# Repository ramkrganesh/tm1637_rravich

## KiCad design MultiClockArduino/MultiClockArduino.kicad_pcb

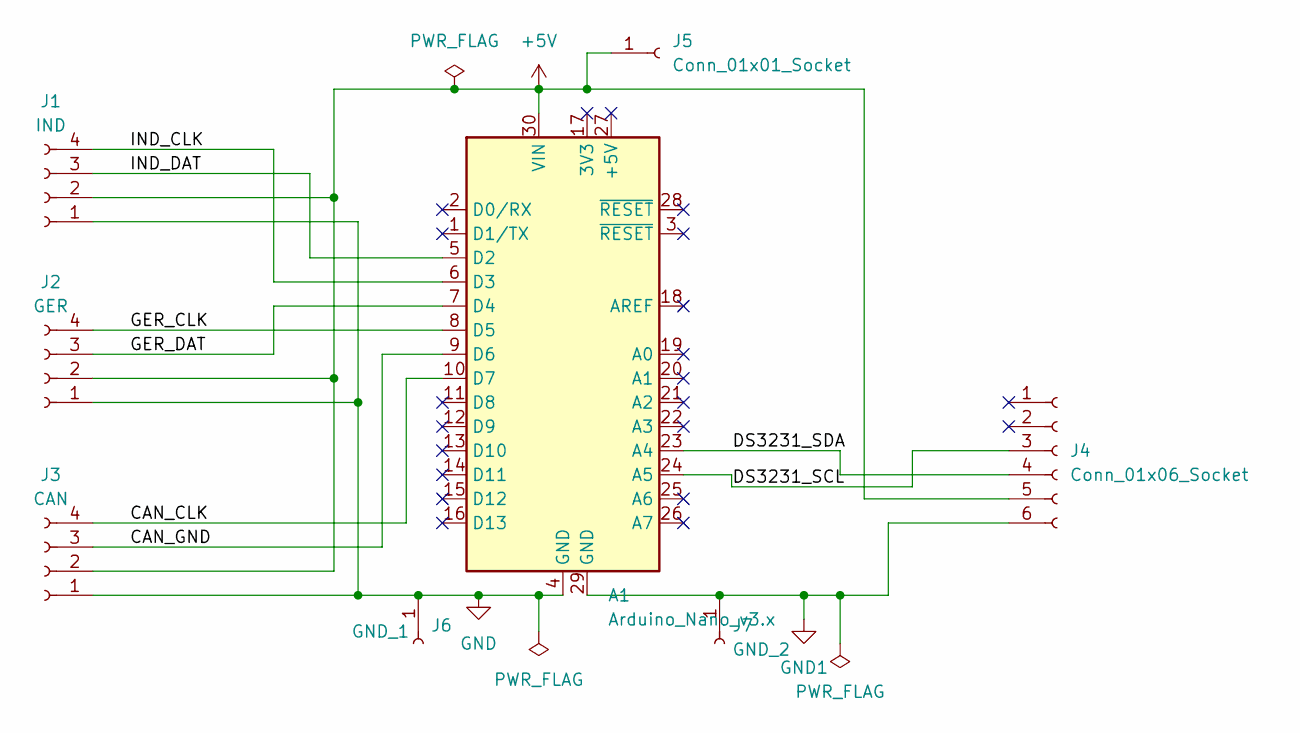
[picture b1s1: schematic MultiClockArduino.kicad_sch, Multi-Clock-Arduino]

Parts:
A1: Arduino_Nano_v3.x; Arduino_Nano
J1: IND; PinSocket_1x04_P2.54mm_Vertical
J2: GER; PinSocket_1x04_P2.54mm_Vertical
J3: CAN; PinSocket_1x04_P2.54mm_Vertical
J4: Conn_01x06_Socket; PinSocket_1x06_P2.54mm_Vertical
J5: Conn_01x01_Socket; PinSocket_1x01_P2.54mm_Vertical
J6: GND_1; PinSocket_1x01_P2.54mm_Vertical
J7: GND_2; PinSocket_1x01_P2.54mm_Vertical

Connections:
+5V: A1.30 (VIN), J1.2, J2.2, J3.2, J4.5, J5.1
/CAN_CLK: A1.10 (D7), J3.4
/CAN_GND: A1.9 (D6), J3.3
/DS3231_SCL: A1.24 (A5), J4.3
/DS3231_SDA: A1.23 (A4), J4.4
/GER_CLK: A1.8 (D5), J2.4
/GER_DAT: A1.7 (D4), J2.3
/IND_CLK: A1.6 (D3), J1.4
/IND_DAT: A1.5 (D2), J1.3
GND: A1.4 (GND), J1.1, J2.1, J3.1, J6.1
GND1: A1.29 (GND), J4.6, J7.1

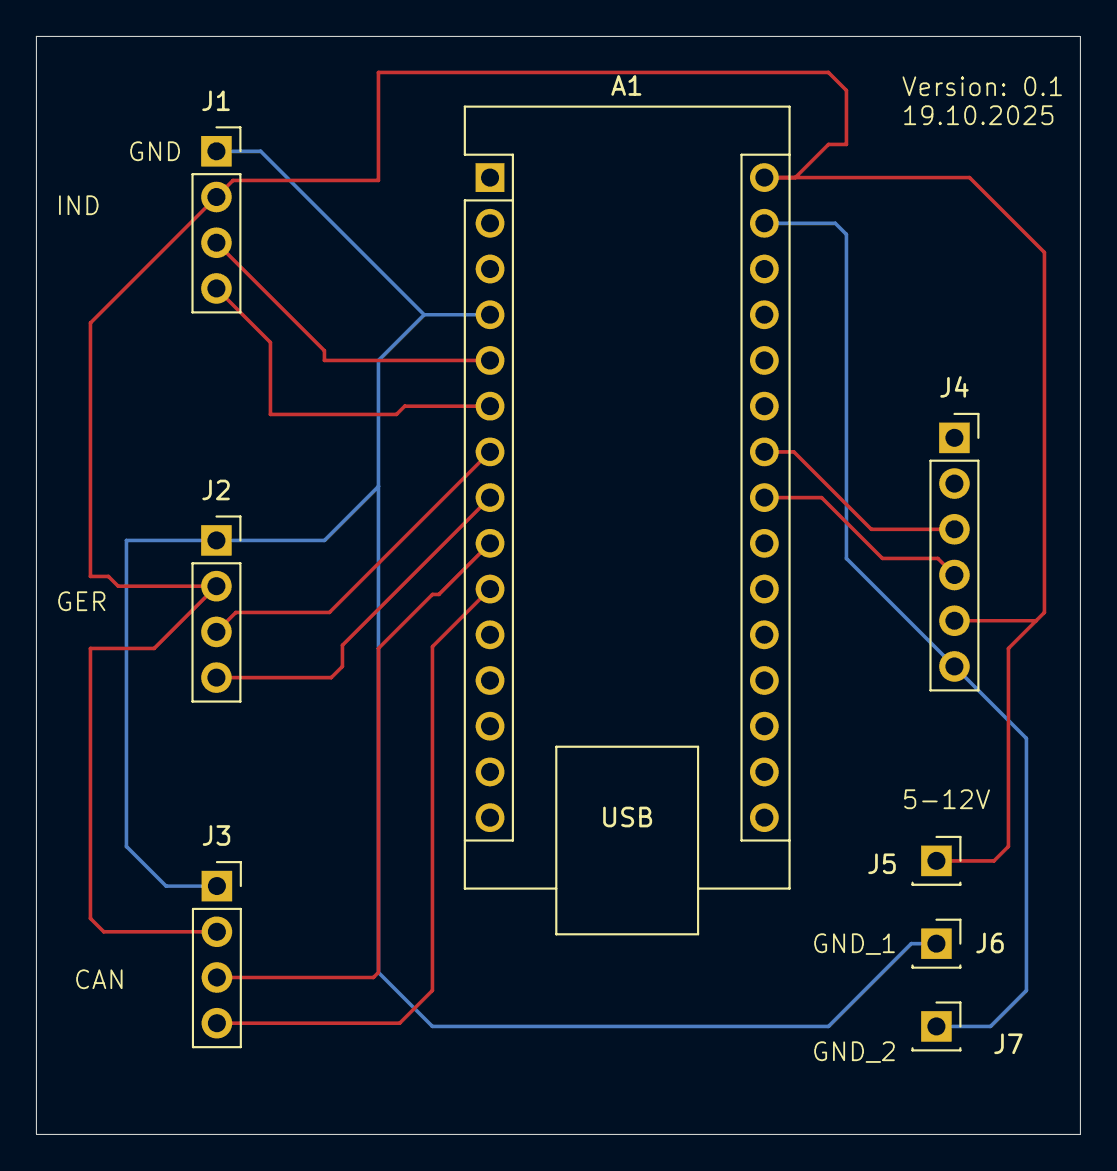
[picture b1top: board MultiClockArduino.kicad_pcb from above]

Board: 2 copper layers, 58.0 x 61.0 mm, 8 parts (0 on the bottom side), 11 nets.

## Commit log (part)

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2025-03-02 Initial commit: base version. Support for One 4 digit clock.
2025-03-02 3 different time displayed in 3 display modules
2025-03-07 rearranged time buffer and fixed bug - now the seconds updates every 1 second.
2025-03-07 adjusted delay; dot bit is now always set
2025-03-08 time updates sent every 1 minute; display is written once and not continuously
2025-03-09 implemented resetting display in case of failure
2025-04-26 usage of DS3231 for time calculation
2025-11-02 fixed bug in hour calculation
2025-11-02 bug fix: to compute hr, bits 0-3 of hr register can be read directly.
2025-11-15 added schematic files and cmake file
2025-11-15 deleted unwanted backup files.
2025-11-15 new time set, bug fix for hour
2025-11-17 Initial time set as 2PM
2025-11-22 bug fix in india time. hr incremented by 1 when minutes > 60
2025-11-22 compiler error fix
